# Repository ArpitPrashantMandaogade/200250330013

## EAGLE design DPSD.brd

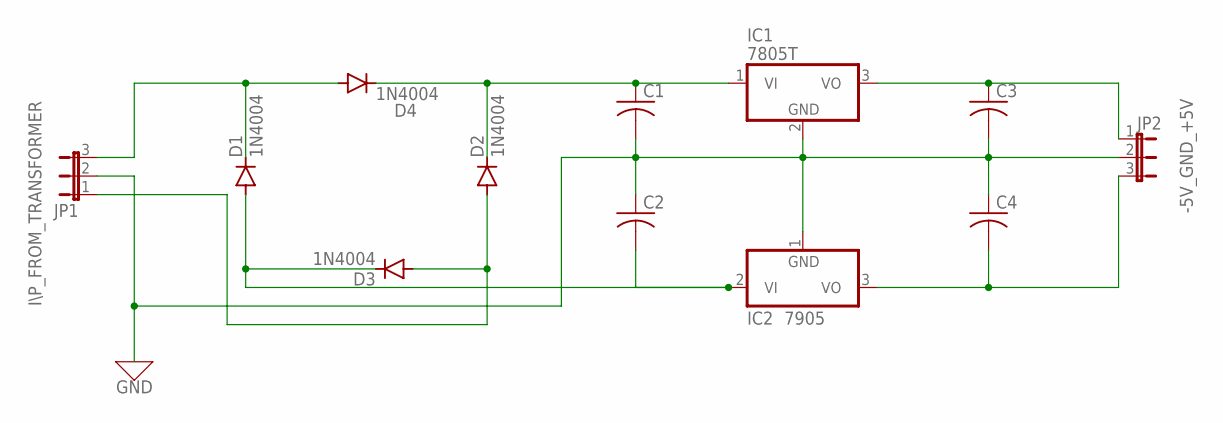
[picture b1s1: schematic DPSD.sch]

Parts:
C1, C2, C3, C4: C-US025-024X044; C025-024X044
D1, D2, D3, D4: 1N4004; DO41-10
IC1: 7805T; TO220H
IC2: 7905T; TO220H
JP1, JP2: JP2E; JP2

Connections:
0: C1.2, C2.1, IC1.2 (GND), IC2.1 (GND), JP1.2, JP2.2
unnamed: D1.C, D4.A, JP1.3
unnamed: C1.1, D2.C, D4.C, IC1.1 (VI)
unnamed: D2.A, D3.A, JP1.1
unnamed: C3.2, C4.1
unnamed: C3.1, IC1.3 (VO), JP2.1
unnamed: C4.2, IC2.3 (VO), JP2.3
unnamed: C2.2, D1.A, D3.C, IC2.2 (VI)

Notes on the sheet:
7905
-5V_GND_+5V
I\P_FROM_TRANSFORMER
GND

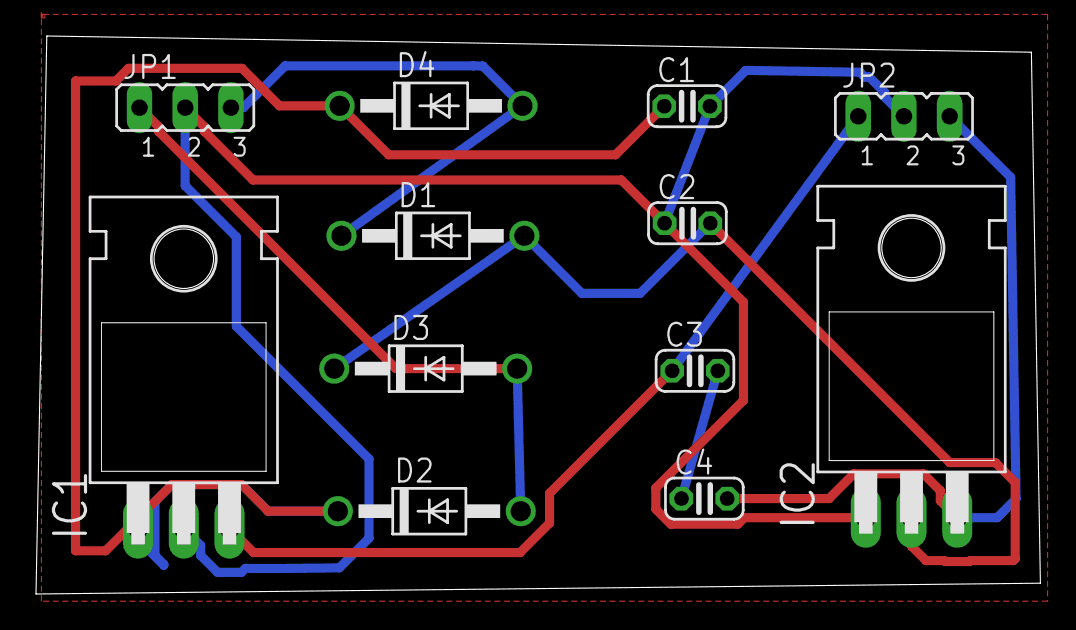
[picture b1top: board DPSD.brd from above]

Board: 2 copper layers, 55.8 x 31.0 mm, 12 parts (0 on the bottom side), 8 nets.

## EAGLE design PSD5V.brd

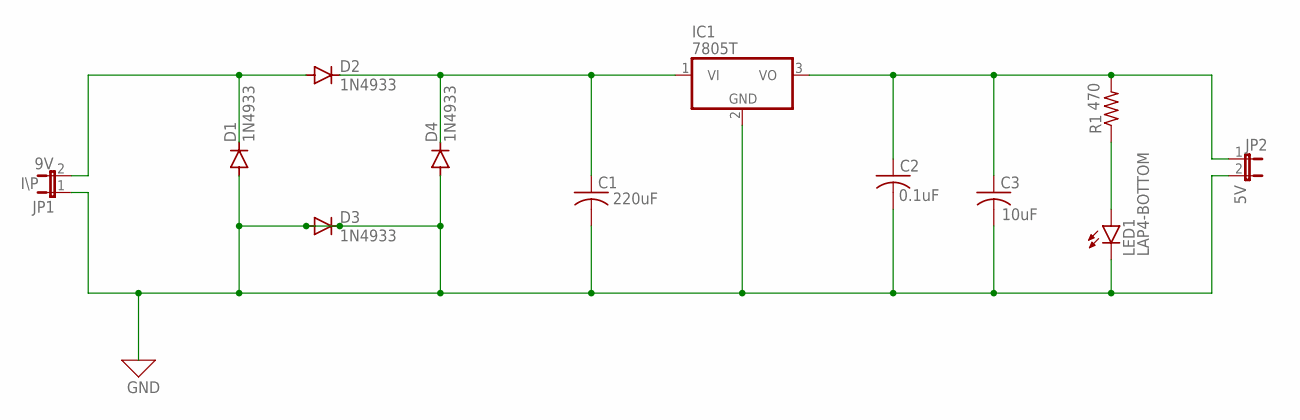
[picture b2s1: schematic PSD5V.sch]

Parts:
C1, C2, C3: C-US025-024X044; C025-024X044
D1, D2, D3, D4: 1N4933; DO41-10
IC1: 7805T; TO220H
JP1, JP2: JP1E; JP1
LED1: LAP4-BOTTOM; P47F-BOTTOM
R1: R-US_0204/7; 0204/7

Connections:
0: C1.2, C2.2, C3.2, D1.A, D3.A, D3.C, D4.A, IC1.2 (GND), JP1.1, JP2.2, LED1.C
unnamed: D1.C, D2.A, JP1.2
unnamed: LED1.A, R1.1
unnamed: C2.1, C3.1, IC1.3 (VO), JP2.1, R1.2
unnamed: C1.1, D2.C, D4.C, IC1.1 (VI)

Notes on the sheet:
I\P
220uF
0.1uF
10uF
470
GND

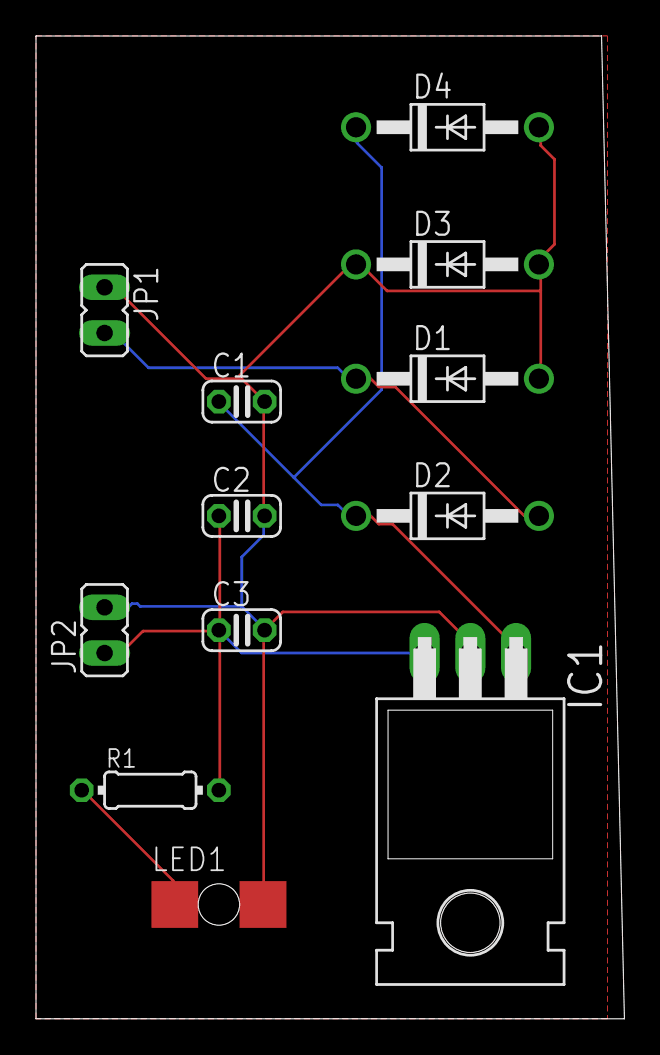
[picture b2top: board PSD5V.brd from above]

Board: 2 copper layers, 32.7 x 54.6 mm, 12 parts (0 on the bottom side), 5 nets.
